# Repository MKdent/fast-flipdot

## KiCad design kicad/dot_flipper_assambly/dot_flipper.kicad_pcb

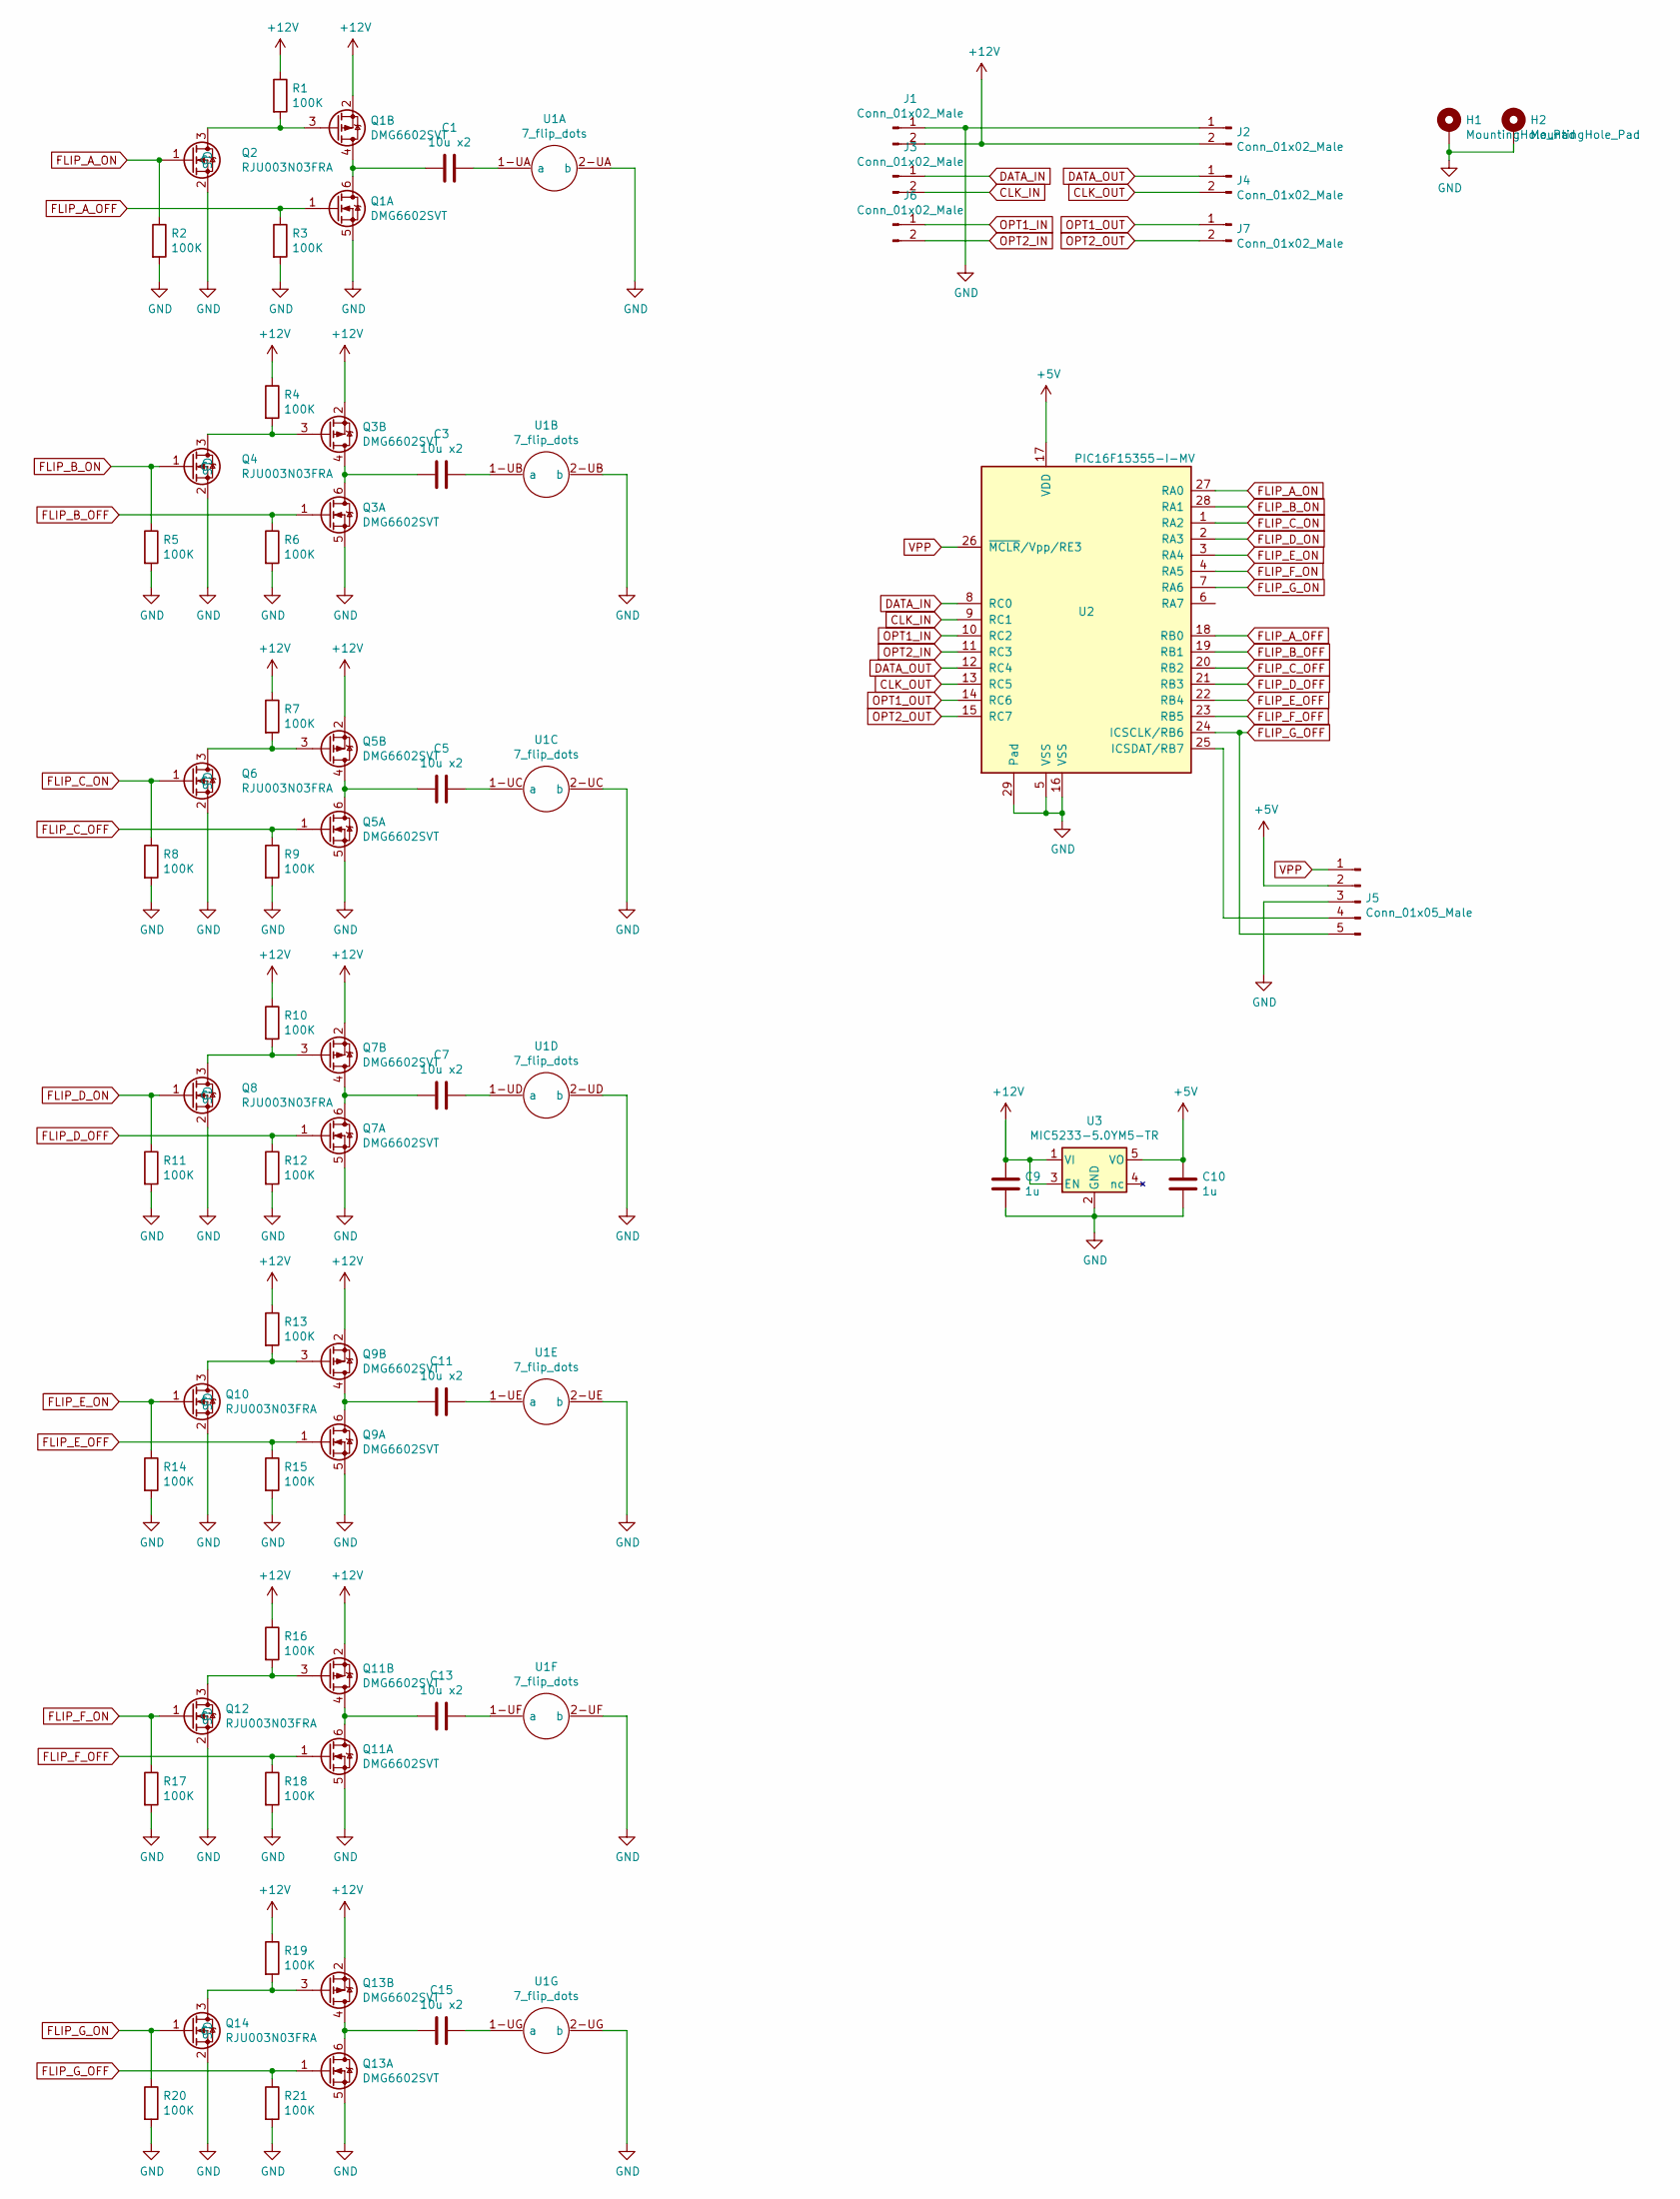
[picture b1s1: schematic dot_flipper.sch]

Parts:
C1, C3, C5, C7, C11, C13, C15: 10u x2; C_1206_3216Metric
C9, C10: 1u; C_0805
H1, H2: MountingHole_Pad; MountingHole_2.2mm_M2_Pad_thin
J1, J2, J3, J4, J6, J7: Conn_01x02_Male; Pin_Header_Straight_1x02_Pitch2.54mm
J5: Conn_01x05_Male; Pin_Header_Straight_1x05_Pitch1.27mm
Q1, Q3, Q5, Q7, Q9, Q11, Q13: DMG6602SVT; SOT-23-6_Handsoldering
Q2, Q4, Q6, Q8, Q10, Q12, Q14: RJU003N03FRA; SOT-323_SC-70
R1, R2, R3, R4, R5, R6, R7, R8, R9, R10, R11, R12, R13, R14, R15, R16, R17, R18, R19, R20, R21: 100K; R_0805
U1: 7_flip_dots
U2: PIC16F15355-I-MV; QFN-28-1EP_4x4mm_Pitch0.4mm_wide
U3: MIC5233-5.0YM5-TR; SOT-23-5_HandSoldering

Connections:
+5V: C10.1, J5.2, U2.17 (VDD), U3.5 (VO)
+12V: C9.1, J1.2, J2.2, Q1.2 (S), Q3.2 (S), Q5.2 (S), Q7.2 (S), Q9.2 (S), Q11.2 (S), Q13.2 (S), R1.1, R4.1, R7.1, R10.1, R13.1, R16.1, R19.1, U3.1 (VI), U3.3 (EN)
CLK_IN: J3.2, U2.9 (RC1)
CLK_OUT: J4.2, U2.13 (RC5)
DATA_IN: J3.1, U2.8 (RC0)
DATA_OUT: J4.1, U2.12 (RC4)
FLIP_A_OFF: Q1.1 (G), R3.1, U2.18 (RB0)
FLIP_A_ON: Q2.1 (G), R2.1, U2.27 (RA0)
FLIP_B_OFF: Q3.1 (G), R6.1, U2.19 (RB1)
FLIP_B_ON: Q4.1 (G), R5.1, U2.28 (RA1)
FLIP_C_OFF: Q5.1 (G), R9.1, U2.20 (RB2)
FLIP_C_ON: Q6.1 (G), R8.1, U2.1 (RA2)
FLIP_D_OFF: Q7.1 (G), R12.1, U2.21 (RB3)
FLIP_D_ON: Q8.1 (G), R11.1, U2.2 (RA3)
FLIP_E_OFF: Q9.1 (G), R15.1, U2.22 (RB4)
FLIP_E_ON: Q10.1 (G), R14.1, U2.3 (RA4)
FLIP_F_OFF: Q11.1 (G), R18.1, U2.23 (RB5)
FLIP_F_ON: Q12.1 (G), R17.1, U2.4 (RA5)
FLIP_G_OFF: J5.5, Q13.1 (G), R21.1, U2.24 (ICSCLK/RB6)
FLIP_G_ON: Q14.1 (G), R20.1, U2.7 (RA6)
GND: C9.2, C10.2, H1.1, H2.1, J1.1, J2.1, J5.3, Q1.5 (S), Q2.2 (S), Q3.5 (S), Q4.2 (S), Q5.5 (S), Q6.2 (S), Q7.5 (S), Q8.2 (S), Q9.5 (S), Q10.2 (S), Q11.5 (S), Q12.2 (S), Q13.5 (S), Q14.2 (S), R2.2, R3.2, R5.2, R6.2, R8.2, R9.2, R11.2, R12.2, R14.2, R15.2, R17.2, R18.2, R20.2, R21.2, U1.2-UA (b), U1.2-UB (b), U1.2-UC (b), U1.2-UD (b), U1.2-UE (b), U1.2-UF (b), U1.2-UG (b), U2.5 (VSS), U2.16 (VSS), U2.29 (Pad), U3.2 (GND)
unnamed: C1.1, U1.1-UA (a)
unnamed: C1.2, Q1.4 (D), Q1.6 (D)
unnamed: C3.1, U1.1-UB (a)
unnamed: C3.2, Q3.4 (D), Q3.6 (D)
unnamed: C5.1, U1.1-UC (a)
unnamed: C5.2, Q5.4 (D), Q5.6 (D)
unnamed: C7.1, U1.1-UD (a)
unnamed: C7.2, Q7.4 (D), Q7.6 (D)
unnamed: C11.1, U1.1-UE (a)
unnamed: C11.2, Q9.4 (D), Q9.6 (D)
unnamed: C13.1, U1.1-UF (a)
unnamed: C13.2, Q11.4 (D), Q11.6 (D)
unnamed: C15.1, U1.1-UG (a)
unnamed: C15.2, Q13.4 (D), Q13.6 (D)
unnamed: J5.4, U2.25 (ICSDAT/RB7)
unnamed: Q1.3 (G), Q2.3 (D), R1.2
unnamed: Q3.3 (G), Q4.3 (D), R4.2
unnamed: Q5.3 (G), Q6.3 (D), R7.2
unnamed: Q7.3 (G), Q8.3 (D), R10.2
unnamed: Q9.3 (G), Q10.3 (D), R13.2
unnamed: Q11.3 (G), Q12.3 (D), R16.2
unnamed: Q13.3 (G), Q14.3 (D), R19.2
OPT1_IN: J6.1, U2.10 (RC2)
OPT1_OUT: J7.1, U2.14 (RC6)
OPT2_IN: J6.2, U2.11 (RC3)
OPT2_OUT: J7.2, U2.15 (RC7)
VPP: J5.1, U2.26 (~MCLR~/Vpp/RE3)

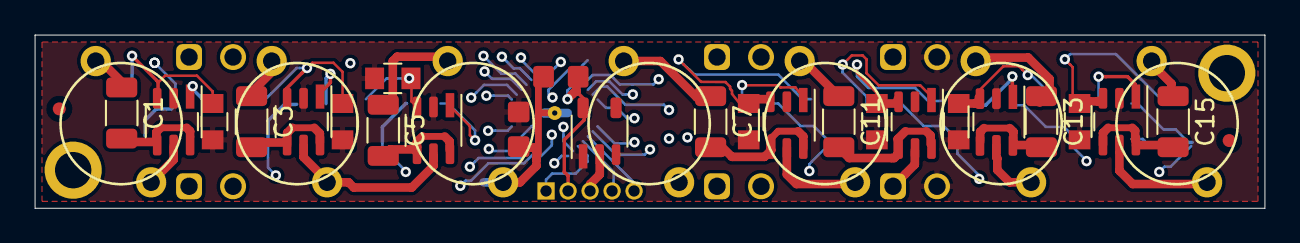
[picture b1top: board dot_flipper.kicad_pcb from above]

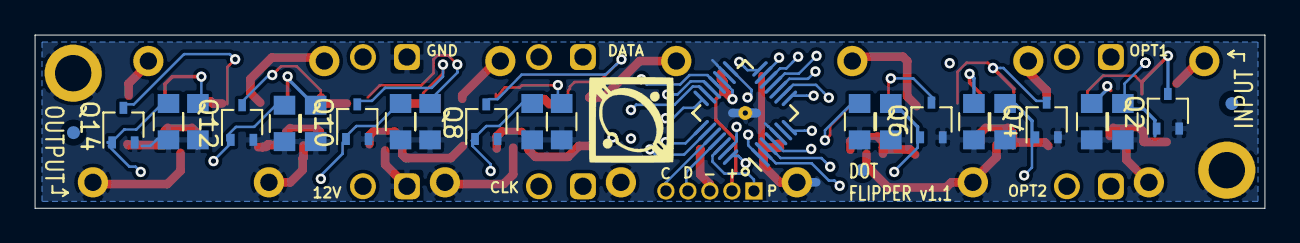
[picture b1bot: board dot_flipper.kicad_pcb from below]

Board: 4 copper layers, 71.0 x 10.0 mm, 56 parts (22 on the bottom side), 48 nets.

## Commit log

2022-01-24 Add files via upload
    kicad files for assembly
2022-01-27 assembly files
